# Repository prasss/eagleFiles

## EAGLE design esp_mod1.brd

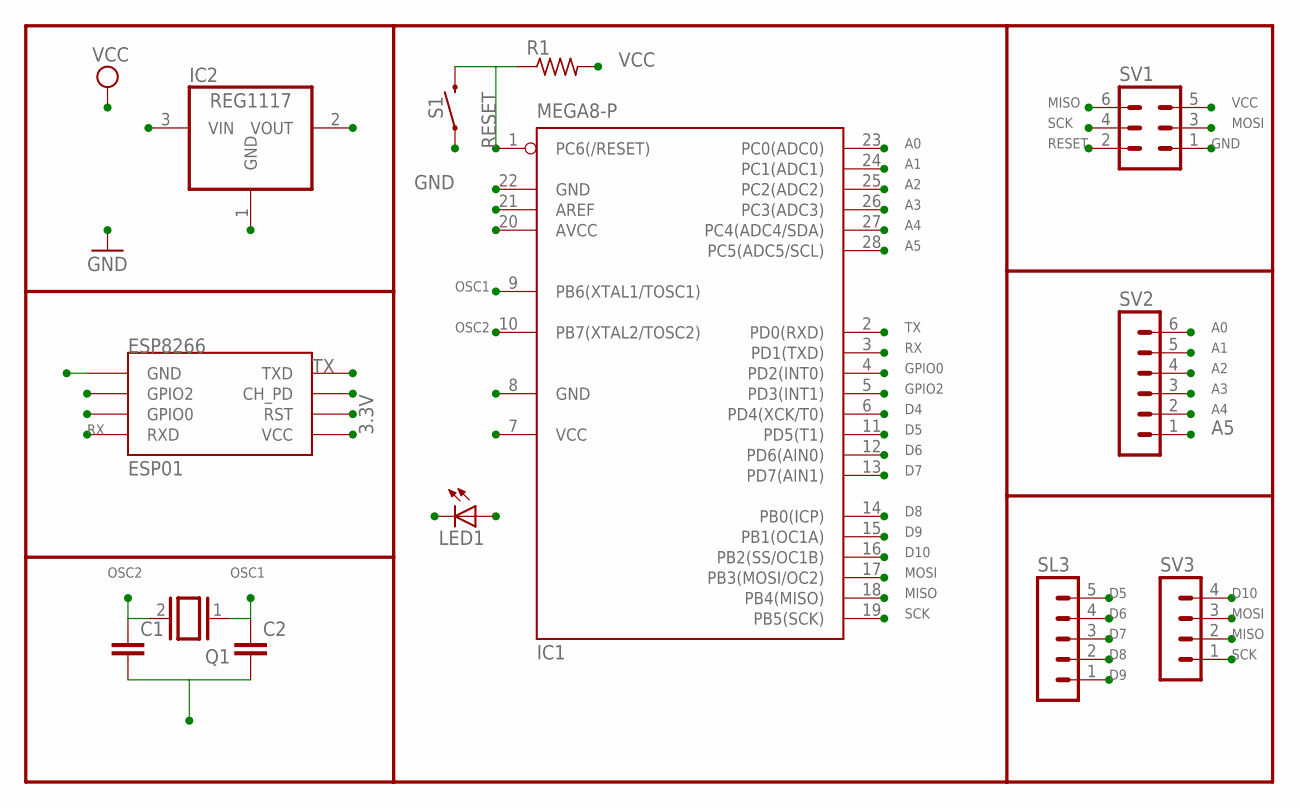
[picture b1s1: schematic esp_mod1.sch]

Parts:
C1, C2: CC1206; C1206
ESP8266: ESP01
IC1: MEGA8-P; DIL28-3
IC2: REG1117; SOT223
LED1: LED_E; LED_1206
Q1: XTAL; Q
R1: R-US_M1206; M1206
S1: MOMENTARY-SWITCH-SPST-PTH-6.0MM; TACTILE_SWITCH_PTH_6.0MM
SL3: MA05-1
SV1: MA03-2
SV2: MA06-1
SV3: MA04-1

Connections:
3.3V: ESP8266.CH_PD, ESP8266.RST, ESP8266.VCC, IC2.2 (VOUT); also elsewhere on the board
A0: IC1.23 (PC0(ADC0)), SV2.6
A1: IC1.24 (PC1(ADC1)), SV2.5
A2: IC1.25 (PC2(ADC2)), SV2.4
A3: IC1.26 (PC3(ADC3)), SV2.3
A4: IC1.27 (PC4(ADC4/SDA)), SV2.2
A5: IC1.28 (PC5(ADC5/SCL)), SV2.1
D4: IC1.6 (PD4(XCK/T0)), LED1.A
D5: IC1.11 (PD5(T1)), SL3.5
D6: IC1.12 (PD6(AIN0)), SL3.4
D7: IC1.13 (PD7(AIN1)), SL3.3
D8: IC1.14 (PB0(ICP)), SL3.2
D9: IC1.15 (PB1(OC1A)), SL3.1
D10: IC1.16 (PB2(SS/OC1B)), SV3.4
GND: C1.2, C2.2, ESP8266.GND, IC1.8 (GND), IC1.22 (GND), IC2.1 (GND), LED1.C, S1.1, SV1.1; also elsewhere on the board
GPIO0: ESP8266.GPIO0, IC1.4 (PD2(INT0)); also elsewhere on the board
GPIO2: ESP8266.GPIO2, IC1.5 (PD3(INT1)); also elsewhere on the board
MISO: IC1.18 (PB4(MISO)), SV1.6, SV3.2
MOSI: IC1.17 (PB3(MOSI/OC2)), SV1.3, SV3.3
OSC1: C2.1, IC1.9 (PB6(XTAL1/TOSC1)), Q1.1
OSC2: C1.1, IC1.10 (PB7(XTAL2/TOSC2)), Q1.2
RESET: IC1.1 (PC6(/RESET)), R1.1, S1.3 (2), SV1.2
RX: ESP8266.RX (RXD), IC1.3 (PD1(TXD)); also elsewhere on the board
SCK: IC1.19 (PB5(SCK)), SV1.4, SV3.1
TX: ESP8266.TX (TXD), IC1.2 (PD0(RXD)); also elsewhere on the board
VCC: IC1.7 (VCC), IC1.20 (AVCC), IC2.3 (VIN), R1.2, SV1.5

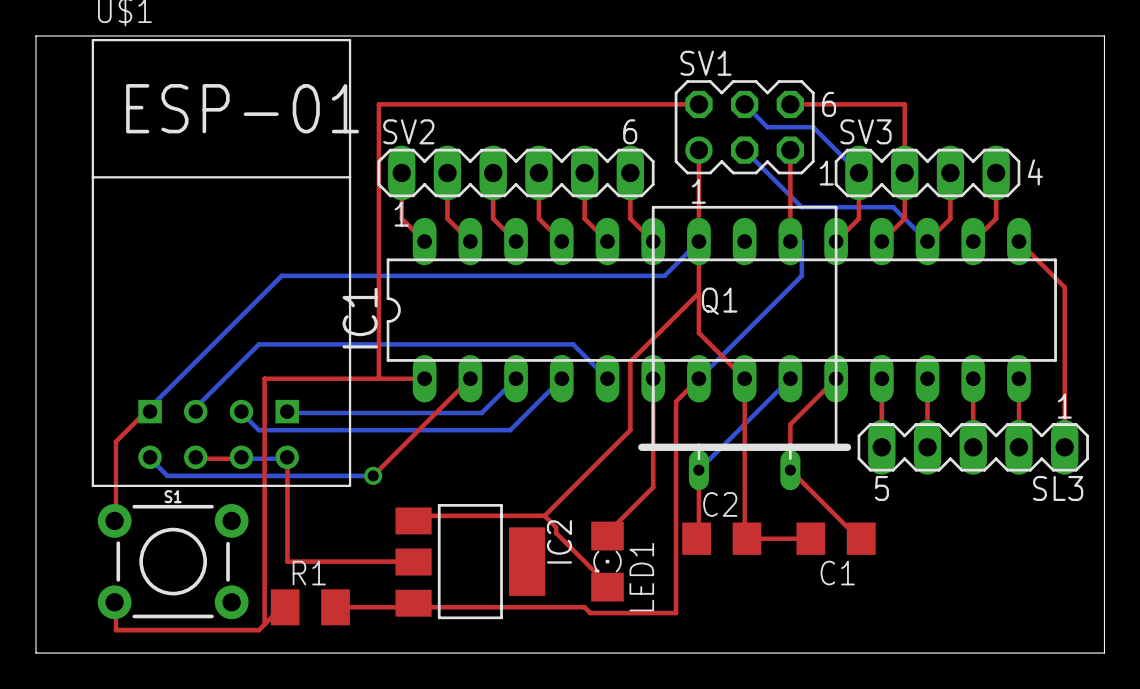
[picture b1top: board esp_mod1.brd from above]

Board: 2 copper layers, 59.4 x 34.3 mm, 13 parts (0 on the bottom side), 26 nets.

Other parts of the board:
U$1: ESP01

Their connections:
3.3V: U$1.CH_PD, U$1.RST, U$1.VCC; also elsewhere on the board
GND: U$1.GND; also elsewhere on the board
GPIO0: U$1.GPIO0; also elsewhere on the board
GPIO2: U$1.GPIO2; also elsewhere on the board
RX: U$1.RX; also elsewhere on the board
TX: U$1.TX; also elsewhere on the board

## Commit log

2018-01-25 commit 1

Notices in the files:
parts and their libraries:
SparkFun-Switches: Licensing: Creative Commons ShareAlike 4.0 International - https://creativecommons.org/licenses/by-sa/4.0
